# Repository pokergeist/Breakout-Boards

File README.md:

# Breakout-Boards

## Introduction

This is my collection of various breakout boards that do one or more of the following:
  * expose a removable MCU board's pins for headers or soldering
  * make edge-pinned boards like Adafruit's ItsyBitsy adaptable to a protoboard
  * add an I2C Qwiic/STEMMA QT port
  * expose debug pins SWDIO and SWCLK (SAMD21/M0) and the option for a Segger J-Link connector.

## Directory Contents

__Board directories__ typically contain the following:
  * Eagle PCB .brd (board) and .sch (schematic) files.
  * all Gerber files for manufacturing in a zip file
  * The schematic rendered as png.
  * Renderings of the board, top and bottom, and maybe a photo of a populated board.

### ItsyBitsy 32u4 3 & 5V MCUs
  * exposes unique pins in (2) 0.3" 16-pin headers so that they can be plugged into a protoboard
  * Qwiic version adds a SMD pad for a 4-cond JST SH Qwiic/STEMMA QT connector and a cut/solder pad for selecting 3 or 5V Qwiic Vcc.
  * The IB Qwiic board have been fabricated so I can soon mark it as Validated.
  * [IB Qwiic README](ItsyBitsy_Qwiic/README.md)
  * [IB Basic README](ItsyBitsy_Basic/README.md)
  * To Do:

### Feather MCU w/ J-Link & Qwiic

#### [Long Form Factor ](Feather_J-Link_Qwiic/README.md)
  * Fabricated and tested to some degree for different projects.

#### [Wide Form Factor](Feather_J-Link_Qwiic/Wide/README.md)
  * Remixed from a long form factor to a wide one.
  * Fabricated and tested.

### Qt Py Breakout w/ J-Link

* This board provides access to all Qt Py and J-Link signals, including the SWDebug pads underneath the Qt Py board.
* Fab pending.

## Adapter Boards

### [Cirque Trackpoint](Adapter_Boards/Cirque_Trackpoint/README.md) FFC-12 to QT Py Adapter Board

The Cirque Trackpoint (e.g., model TM035035) is a circular capacitive touch sensor module available in different diameters supporting SPI and I2C MCU interfacing. In this instance, the board has solder pads for an Adafruit QT Py SAMD21 M0+ (#4600).

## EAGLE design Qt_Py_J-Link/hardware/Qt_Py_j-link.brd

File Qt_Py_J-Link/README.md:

# Qt Py Breakout with J-Link

This board breaks out the pins for Adafruit's Qt Py SAMD21 Cortex M0 ([#4600](https://www.adafruit.com/product/4600)) board. Additionally, it provide through-hole access to the SWDebug pads underneath using Pogo pin style probes or wires. Headers pins for all Qt Py pins and J-Link signals can be added as well as a J-Link IDC connector.

## Files

Eagle board and schematic files are provided, as well as the zip file containing the Gerber files necessary for fabrication.

## Board Status

|    Date    | Status                                                       |
| :--------: | ------------------------------------------------------------ |
| 2022-22-27 | Uploading rev 1b board with correctly sized QT Py through holes. |
| 2022-09-21 | This board is about to be released for fabrication and is therefore<br/>unverified (especially the SWD pads). |

## Board Images

## Schematic

<u></u>

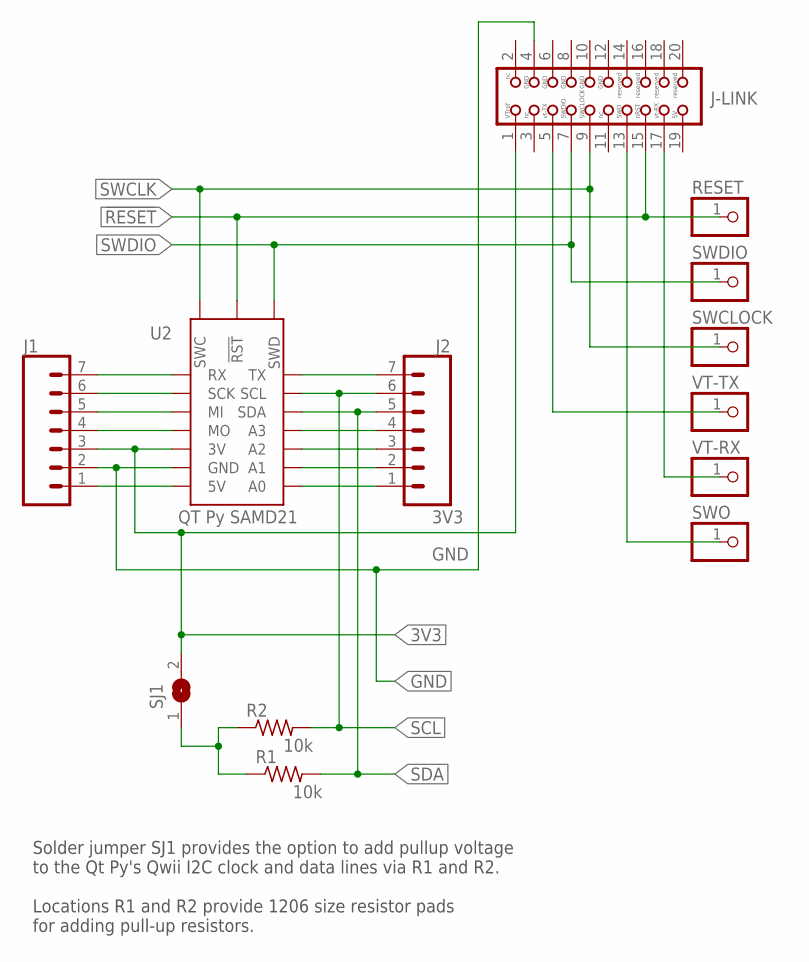
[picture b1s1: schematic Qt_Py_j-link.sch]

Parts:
J1, J2: CONN_07; 1X07
J-LINK: JLINK-ARM; JTAG-ARM
R1, R2: 10k; M1206
RESET: PINHD-1X1; 1X01
SJ1: SJ-OPEN; SJ
SWCLOCK: PINHD-1X1; 1X01
SWDIO: PINHD-1X1; 1X01
SWO: PINHD-1X1; 1X01
U2: QT Py SAMD21; QT_PY-SWD-TH
VT-RX: PINHD-1X1; 1X01
VT-TX: PINHD-1X1; 1X01

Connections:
3V3: J1.3, J-LINK.1, SJ1.2, U2.3V3@1 (3V), U2.3V3@2 (3V)
5V: J1.1, U2.5V@1 (5V), U2.5V@2 (5V)
!RESET: J-LINK.15, RESET.1, U2.!RESET (!RST)
A0: J2.1, U2.A0@1 (A0), U2.A0@2 (A0)
GND: J1.2, J-LINK.4, U2.GND@1 (GND), U2.GND@2 (GND)
unnamed: J1.7, U2.RX@1 (RX), U2.RX@2 (RX)
unnamed: J1.6, U2.SCLK@1 (SCK), U2.SCLK@2 (SCK)
unnamed: J1.5, U2.MISO@1 (MI), U2.MISO@2 (MI)
unnamed: J1.4, U2.MOSI@1 (MO), U2.MOSI@2 (MO)
unnamed: J2.4, U2.A3@1 (A3), U2.A3@2 (A3)
unnamed: J2.2, U2.A1@1 (A1), U2.A1@2 (A1)
unnamed: J2.3, U2.A2@1 (A2), U2.A2@2 (A2)
unnamed: J2.7, U2.TX@1 (TX), U2.TX@2 (TX)
PULL-UP: R1.1, R2.1, SJ1.1
SCL: J2.6, R2.2, U2.SCL@1 (SCL), U2.SCL@2 (SCL)
SDA: J2.5, R1.2, U2.SDA@1 (SDA), U2.SDA@2 (SDA)
SWCLK: J-LINK.9, SWCLOCK.1, U2.SWCLK (SWC)
SWDIO: J-LINK.7, SWDIO.1, U2.SWDIO (SWD)
SWO: J-LINK.13, SWO.1
VT-RX: J-LINK.17, VT-RX.1
VT-TX: J-LINK.5, VT-TX.1

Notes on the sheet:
Solder jumper SJ1 provides the option to add pullup voltage to the Qt Py's Qwii I2C clock and data lines via R1 and R2. Locations R1 and R2 provide 1206 size resistor pads for adding pull-up resistors.

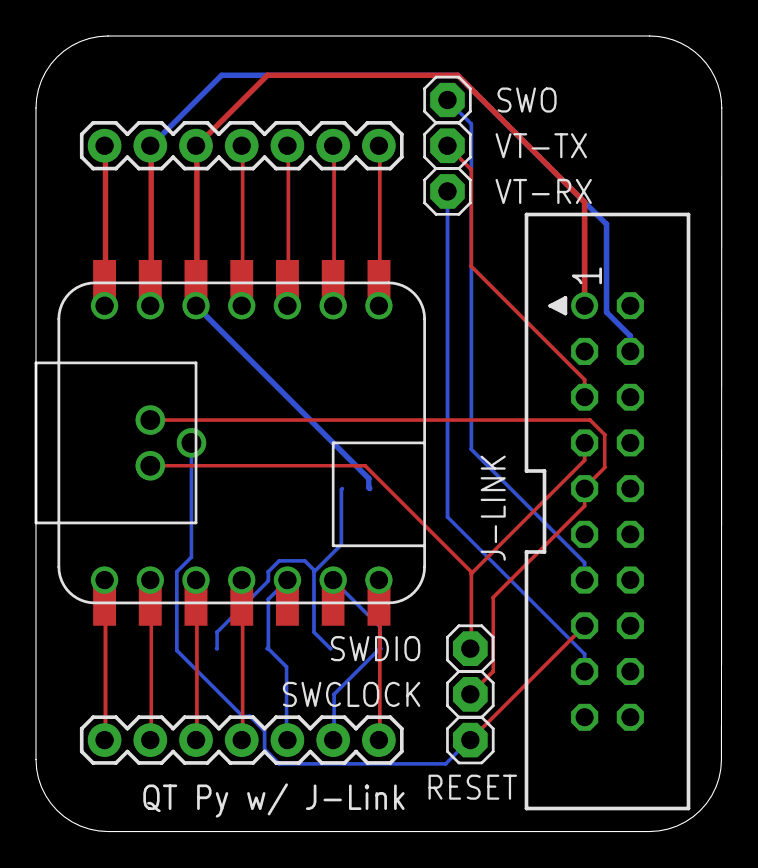
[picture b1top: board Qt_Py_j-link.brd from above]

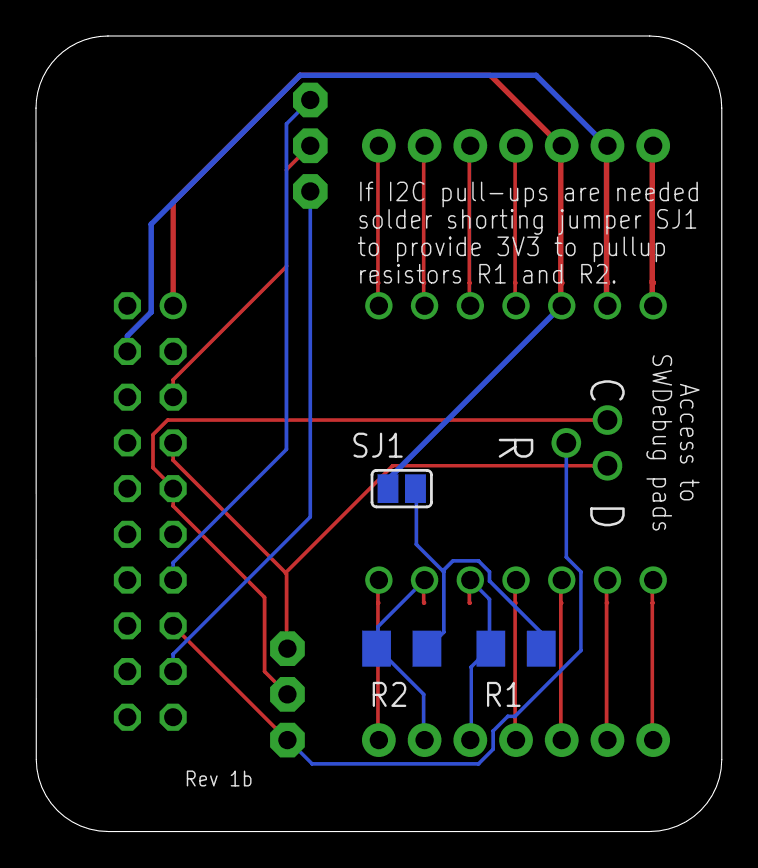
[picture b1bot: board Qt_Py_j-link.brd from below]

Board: 2 copper layers, 38.1 x 44.2 mm, 13 parts (3 on the bottom side), 21 nets.

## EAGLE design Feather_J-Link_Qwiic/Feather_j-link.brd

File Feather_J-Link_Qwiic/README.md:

# Feather w/ J-Link & Qwiic
  * Provides:
    * access to:
      * all Feather pins
      * SWDIO and SWCLOCK software debugging pins
    * the option for adding a Segger J-Link connector and access to its additional pins
    * solder pads for a Qwiic/STEMMA QT I2C connector
    * solder pads for I2C pull-up resistors (SMD 1206 size)
  * Fabricated and tested to some degree for different projects.

## Directory Contents

__Board directories__ typically contain the following:
  * Eagle PCB .brd (board) and .sch (schematic) files.
  * all Gerber files for manufacturing in a zip file
  * The schematic rendered as PDF.
  * Renderings of the board, top and bottom, and maybe a photo of a populated board.

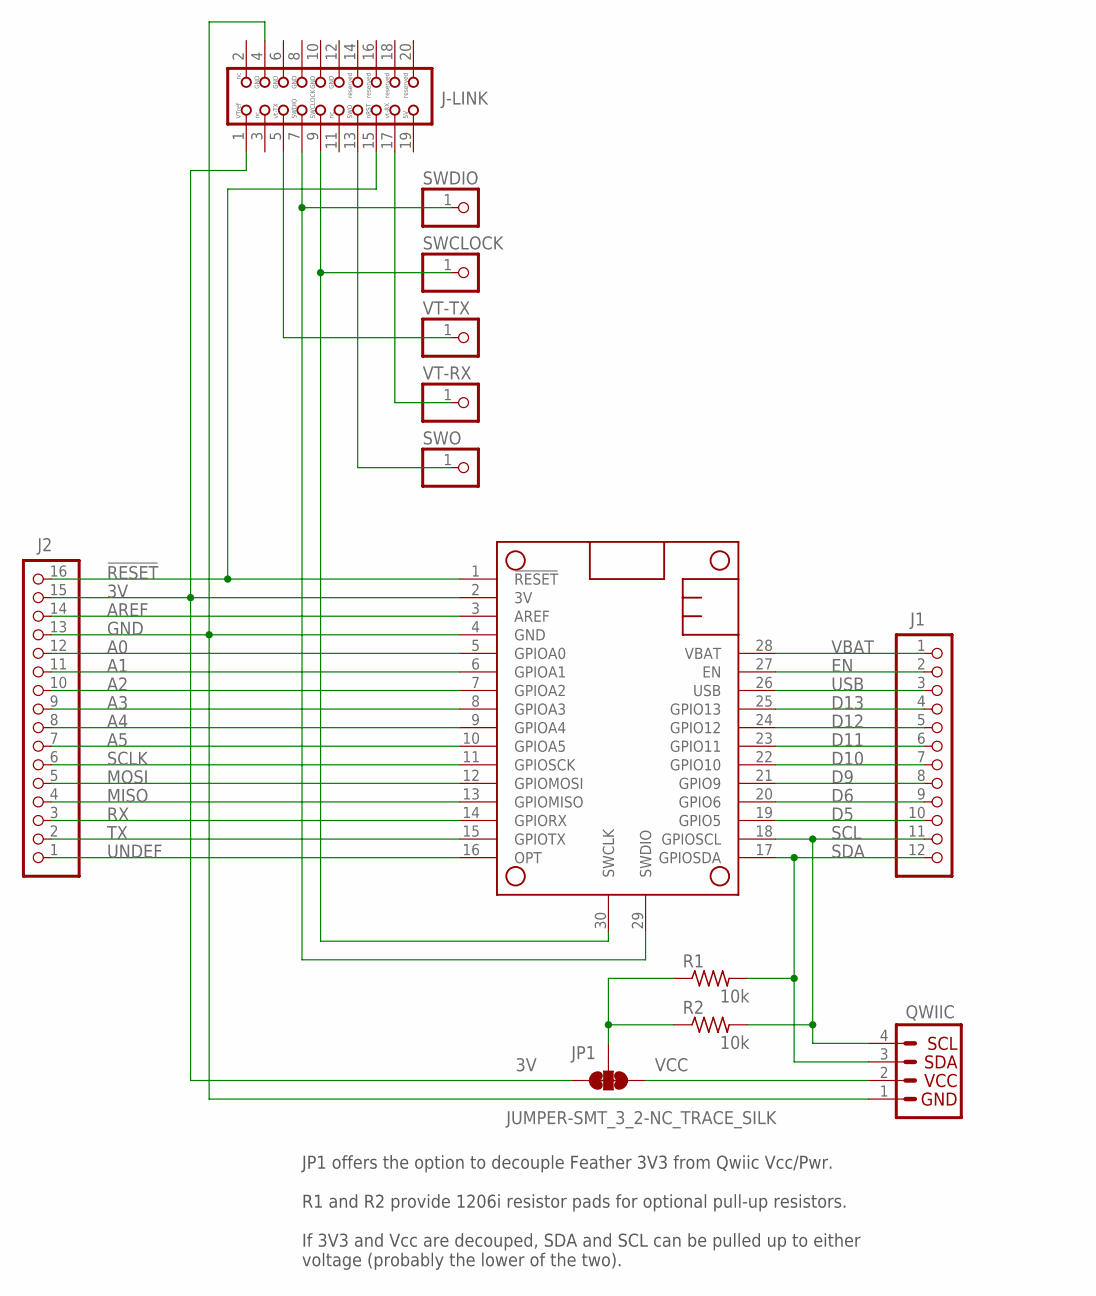
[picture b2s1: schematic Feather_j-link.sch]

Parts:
J1: HEADER-1X1276MIL; 1X12_ROUND_76MIL
J2: HEADER-1X16ROUND; 1X16_ROUND
J-LINK: JLINK-ARM; JTAG-ARM
JP1: JUMPER-SMT_3_2-NC_TRACE_SILK; SMT-JUMPER_3_2-NC_TRACE_SILK
MS2: FEATHERWING-SWD-SWD; FEATHERWING_DIM_SWD
QWIIC: QWIIC_CONNECTORJS-1MM; 1X04_1MM_RA
R1, R2: 10k; M1206
SWCLOCK: PINHD-1X1; 1X01
SWDIO: PINHD-1X1; 1X01
SWO: PINHD-1X1; 1X01
VT-RX: PINHD-1X1; 1X01
VT-TX: PINHD-1X1; 1X01

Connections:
3V: J2.15, J-LINK.1, JP1.3, MS2.2 (3V)
!RESET: J2.16, J-LINK.15, MS2.1 (!RESET)
A0: J2.12, MS2.5 (GPIOA0)
A1: J2.11, MS2.6 (GPIOA1)
A2: J2.10, MS2.7 (GPIOA2)
A3: J2.9, MS2.8 (GPIOA3)
A4: J2.8, MS2.9 (GPIOA4)
A5: J2.7, MS2.10 (GPIOA5)
AREF: J2.14, MS2.3 (AREF)
D5: J1.10, MS2.19 (GPIO5)
D6: J1.9, MS2.20 (GPIO6)
D9: J1.8, MS2.21 (GPIO9)
D10: J1.7, MS2.22 (GPIO10)
D11: J1.6, MS2.23 (GPIO11)
D12: J1.5, MS2.24 (GPIO12)
D13: J1.4, MS2.25 (GPIO13)
EN: J1.2, MS2.27 (EN)
GND: J2.13, J-LINK.4, MS2.4 (GND), QWIIC.1 (GND)
MISO: J2.4, MS2.13 (GPIOMISO)
MOSI: J2.5, MS2.12 (GPIOMOSI)
PULL-UP: JP1.2, R1.1, R2.1
RX: J2.3, MS2.14 (GPIORX)
SCL: J1.11, MS2.18 (GPIOSCL), QWIIC.4 (SCL), R2.2
SCLK: J2.6, MS2.11 (GPIOSCK)
SDA: J1.12, MS2.17 (GPIOSDA), QWIIC.3 (SDA), R1.2
SWCLOCK: J-LINK.9, MS2.30 (SWCLK), SWCLOCK.1
SWDIO: J-LINK.7, MS2.29 (SWDIO), SWDIO.1
SWO: J-LINK.13, SWO.1
TX: J2.2, MS2.15 (GPIOTX)
UNDEF: J2.1, MS2.16 (OPT)
USB: J1.3, MS2.26 (USB)
VBAT: J1.1, MS2.28 (VBAT)
VCC: JP1.1, QWIIC.2 (VCC)
VT-RX: J-LINK.17, VT-RX.1
VT-TX: J-LINK.5, VT-TX.1

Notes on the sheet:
JP1 offers the option to decouple Feather 3V3 from Qwiic Vcc/Pwr. R1 and R2 provide 1206i resistor pads for optional pull-up resistors. If 3V3 and Vcc are decouped, SDA and SCL can be pulled up to either voltage (probably the lower of the two).

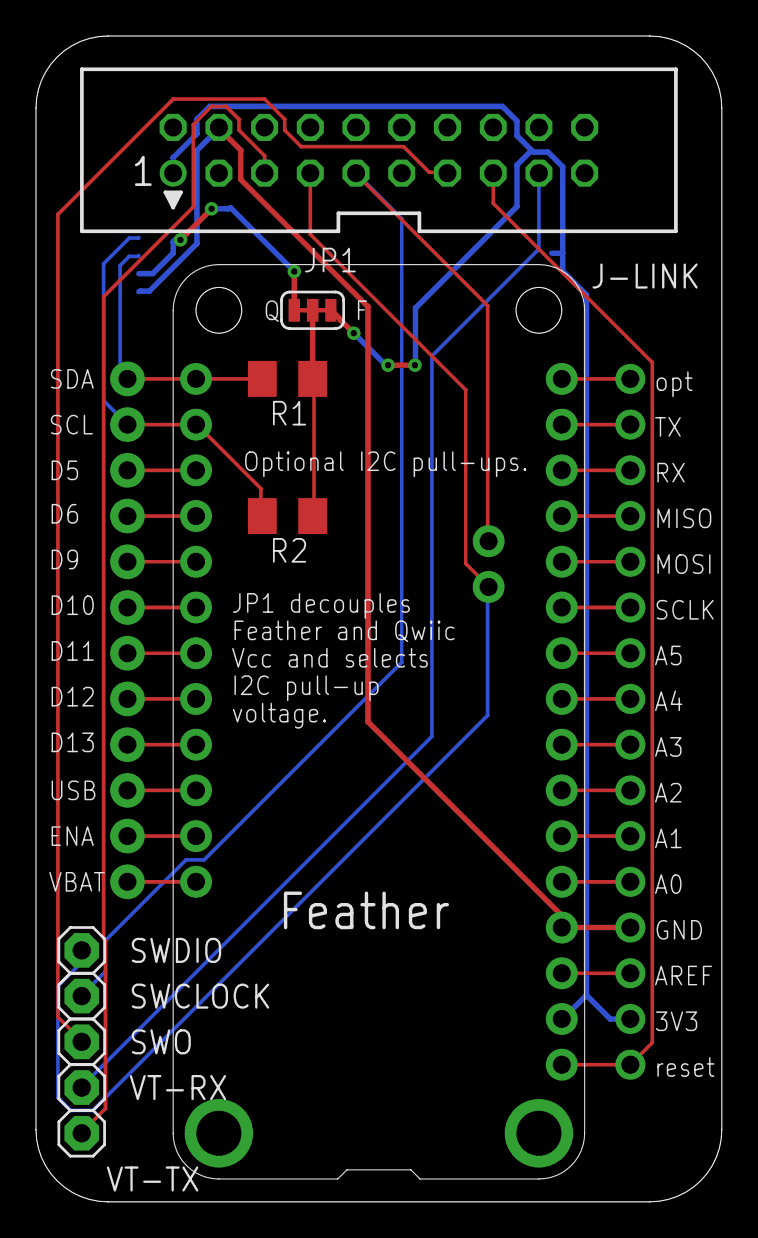
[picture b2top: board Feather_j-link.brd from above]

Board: 2 copper layers, 38.1 x 64.8 mm, 13 parts (1 on the bottom side), 35 nets.

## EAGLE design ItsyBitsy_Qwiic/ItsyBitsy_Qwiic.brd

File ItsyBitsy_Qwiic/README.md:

# ItsyBitsy 32u4 3 & 5V
  * exposes unique pins in (2) 0.3" 16-pin headers so that they can be plugged into a protoboard
  * Qwiic version adds a SMD pad for a 4-cond JST SH Qwiic/STEMMA QT connector and a cut/solder pad for selecting 3 or 5V Qwiic Vcc.
  * The IB Qwiic board have been fabricated so I can soon mark it as Validated.
  * To Do:

__Board directories__ typically contain the following:
  * Eagle PCB .brd (board) and .sch (schematic) files.
  * all Gerber files for manufacturing in a zip file
  * The schematic rendered as PDF.
  * Renderings of the board, top and bottom, and maybe a photo of a populated board.

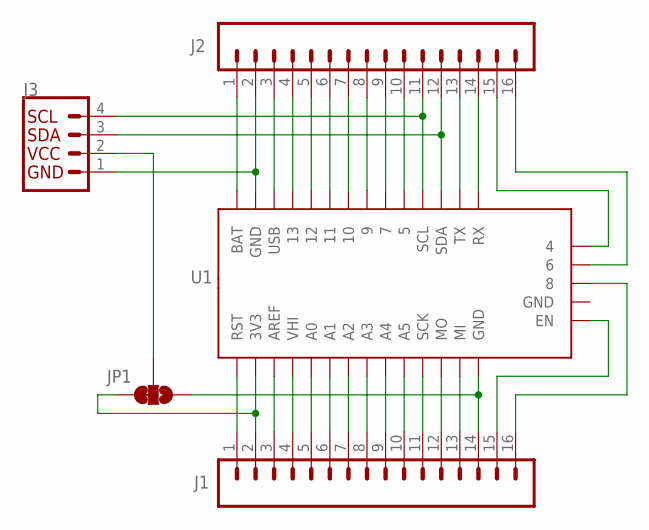
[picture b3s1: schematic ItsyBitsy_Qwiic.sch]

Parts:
J1, J2: CONN_161X16_NO_SILK; 1X16_NO_SILK
J3: QWIIC_CONNECTORJS-1MM; 1X04_1MM_RA
JP1: JUMPER-SMT_3_1-NC_TRACE_SILK; SMT-JUMPER_3_1-NC_TRACE_SILK
U1: ITSYBITSY-32U4-3V; ITSYBITYS-32U4

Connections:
3V-5V: J1.2, JP1.3, U1.P$2 (3V3)
4: J2.15, U1.P$19 (4)
5: J2.10, U1.P$24 (5)
6: J2.16, U1.P$18 (6)
7: J2.9, U1.P$25 (7)
8: J1.16, U1.P$17 (8)
9: J2.8, U1.P$26 (9)
10: J2.7, U1.P$27 (10)
11: J2.6, U1.P$28 (11)
12: J2.5, U1.P$29 (12)
13: J2.4, U1.P$30 (13)
A0: J1.5, U1.P$5 (A0)
A1: J1.6, U1.P$6 (A1)
A2: J1.7, U1.P$7 (A2)
A3: J1.8, U1.P$8 (A3)
A4: J1.9, U1.P$9 (A4)
A5: J1.10, U1.P$10 (A5)
AREF: J1.3, U1.P$3 (AREF)
BAT: J2.1, U1.P$33 (BAT)
EN: J1.15, U1.P$15 (EN)
GND: J2.2, J3.1 (GND), U1.P$16 (GND), U1.P$32 (GND)
GND-3V: J1.14, JP1.1, U1.P$14 (GND)
M0: J1.12, U1.P$12 (MO)
MI: J1.13, U1.P$13 (MI)
RST: J1.1, U1.P$1 (RST)
RX: J2.14, U1.P$20 (RX)
SCK: J1.11, U1.P$11 (SCK)
SCL: J2.11, J3.4 (SCL), U1.P$23 (SCL)
SDA: J2.12, J3.3 (SDA), U1.P$22 (SDA)
TX: J2.13, U1.P$21 (TX)
USB: J2.3, U1.P$31 (USB)
VCC-QWIIC: J3.2 (VCC), JP1.2
VHI-GND: J1.4, U1.P$4 (VHI)

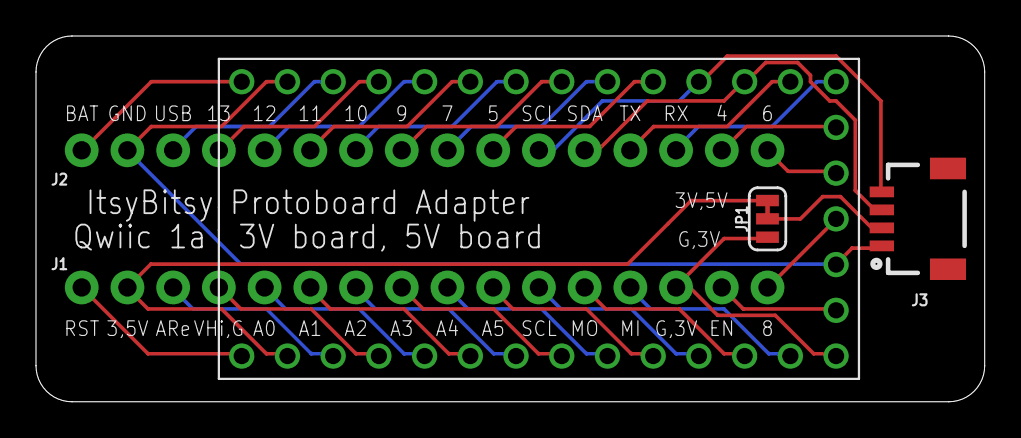
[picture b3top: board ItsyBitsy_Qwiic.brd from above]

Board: 2 copper layers, 52.7 x 20.3 mm, 5 parts (0 on the bottom side), 33 nets.

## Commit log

2022-04-05 Update README.md
    Initial creation
2022-04-05 ci ItsyBitsy protoboard adapters
2022-04-05 renamed subdirs
2022-04-05 rename & small images
2022-04-05 Update README.md
    resized images for preview
2022-04-05 Update README.md
    Last two bullets.
2022-04-05 labeled JP1
2022-04-05 Update README.md
    Reviewed headers, labeled JP1
2022-04-09 enlarged ItsyBitsy holes, add CAM/Gerber zip file
2022-04-10 Update README.md
    Boards submitted for fabrication.
2022-04-10 adding Feather w/ J-Link & Qwiic
2022-04-10 adding images
2022-04-10 Feather images
2022-04-10 typo
2022-04-11 adding schematic images
2022-04-19 Added IBQ photo, updated readme.
2022-04-19 preview helps
2022-04-19 added description of available files
2022-04-20 first ci
2022-04-20 new text
2022-04-20 typos
2022-04-20 new images
2022-04-20 board image
2022-04-20 url fix
2022-04-20 info & image
2022-04-21 new readme files
2022-04-24 links to boards
2022-04-29 new wide format
2022-04-29 link to schematic
2022-09-10 assembled photo
2022-09-21 adding Qt Py Breakout
2022-09-21 added Qt Py breakout and status
2022-09-21 fix Qt Py image links
2022-09-21 resized Qt Py board images
2022-09-21 image link
2022-09-21 link labels
2022-09-21 fixed case in img links
2022-09-21 change filename case the hard way
2022-09-21 back to J-Link
2022-09-21 renaming img files again
2022-09-21 rename done
2022-11-27 reworked QT Py holes

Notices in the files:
parts and their libraries:
microbuilder: This work is placed in the public domain, and may be freely used for commercial and non-commercial work with the following conditions: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
SparkFun-Connectors: Licensing: Creative Commons ShareAlike 4.0 International - https://creativecommons.org/licenses/by-sa/4.0
